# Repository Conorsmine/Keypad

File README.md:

# Keypad
Current progress on the project:

## Resources
ai03 Guide:       https://wiki.ai03.com/books/pcb-design/page/pcb-guide-part-5---creating-the-pcb  
Masterzen Guide:  https://www.masterzen.fr/2020/10/20/designing-a-keyboard-part3/

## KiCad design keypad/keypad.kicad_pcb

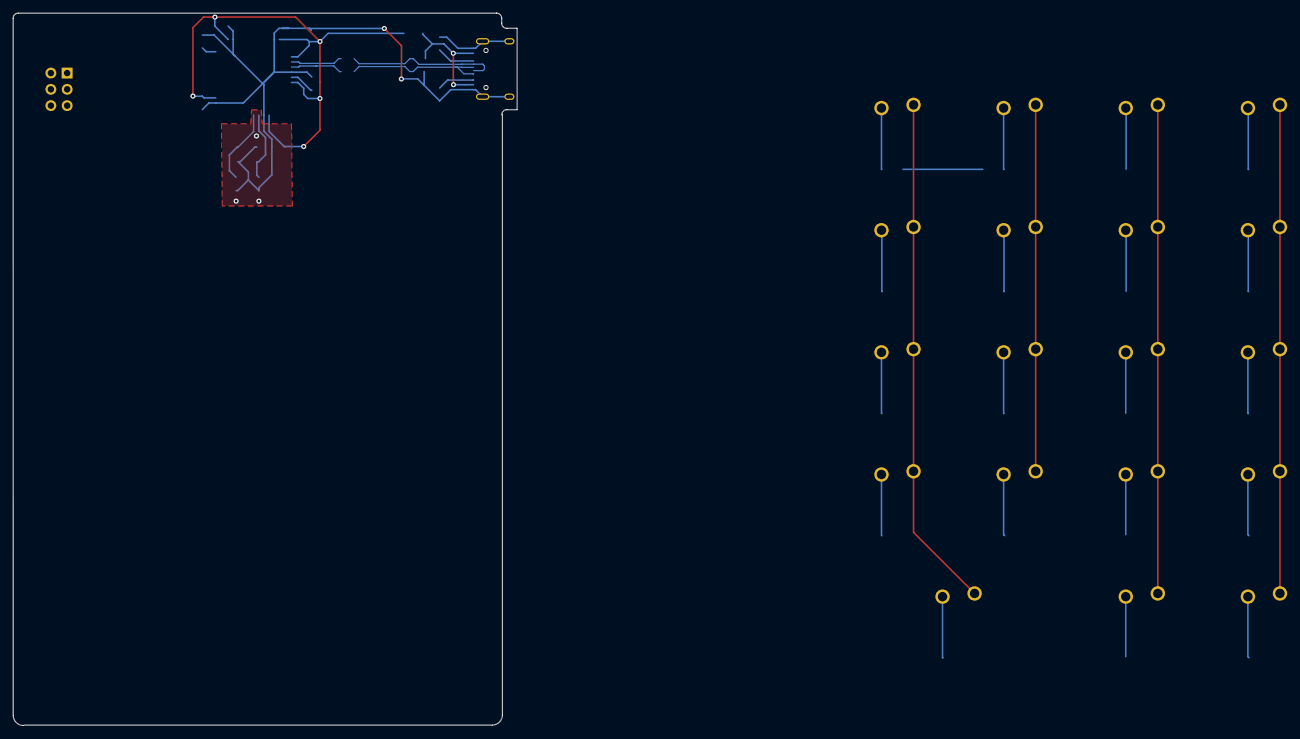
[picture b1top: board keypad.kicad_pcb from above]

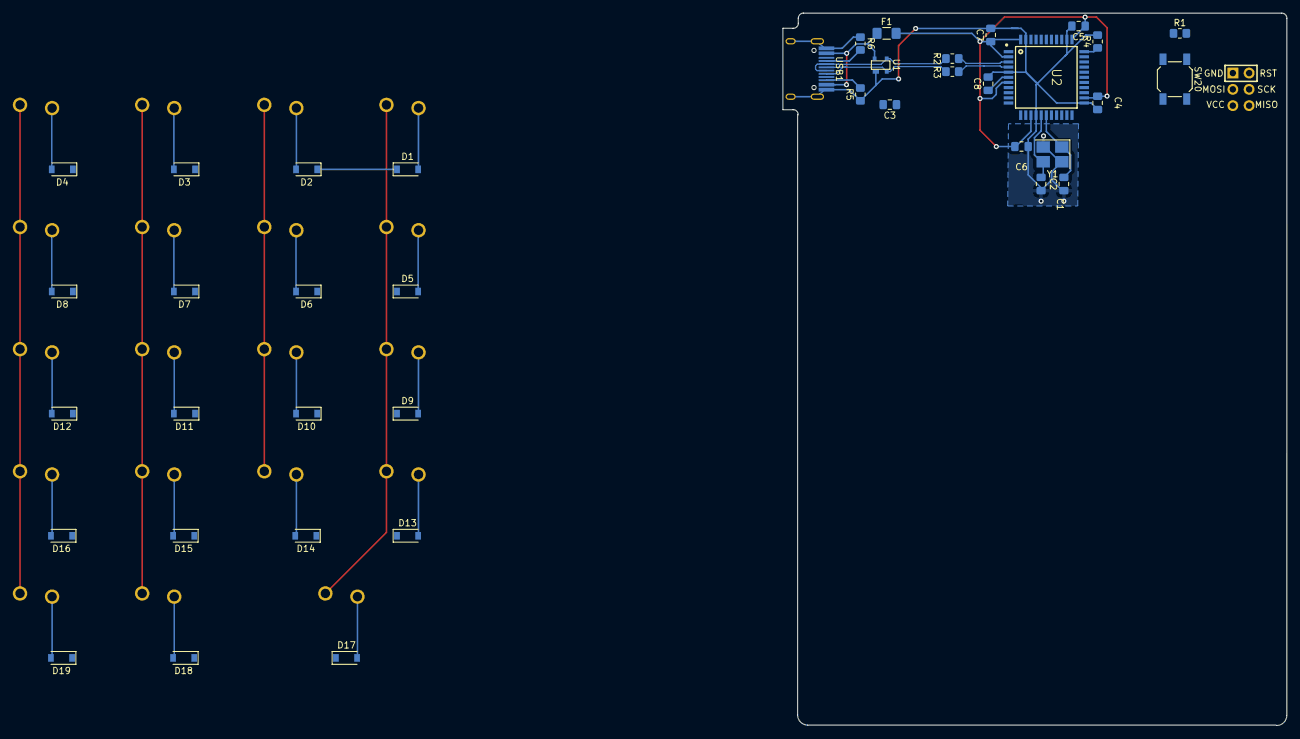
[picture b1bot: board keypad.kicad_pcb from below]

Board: 2 copper layers, 78.6 x 111.1 mm, 59 parts (40 on the bottom side), 45 nets.

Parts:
C1, C2: 22p; C_0805_2012Metric_Pad1.18x1.45mm_HandSolder
C3, C4, C5, C6: 0.1u; C_0805_2012Metric_Pad1.18x1.45mm_HandSolder
C7: 10u; C_0805_2012Metric_Pad1.18x1.45mm_HandSolder
C8: 1u; C_0805_2012Metric_Pad1.18x1.45mm_HandSolder
D1, D2, D3, D4, D5, D6, D7, D8, D9, D10, D11, D12, D13, D14, D15, D16, D17, D18, D19: D; D_SOD-123
F1: 500mA; Fuse_1206_3216Metric_Pad1.42x1.75mm_HandSolder
J1: AVR-ISP-6; Reset_Pretty-Mask
R1, R4: 10k; R_0805_2012Metric_Pad1.20x1.40mm_HandSolder
R2, R3: 22; R_0805_2012Metric_Pad1.20x1.40mm_HandSolder
R5, R6: 5.1k; R_0805_2012Metric_Pad1.20x1.40mm_HandSolder
SW1: num; ALPS-1U
SW2: div; ALPS-1U
SW3: mult; ALPS-1U
SW4: min; ALPS-1U
SW5: #7; ALPS-1U
SW6: #8; ALPS-1U
SW7: #9; ALPS-1U
SW8: plu0; ALPS-1U
SW9: #4; ALPS-1U
SW10: #5; ALPS-1U
SW11: #6; ALPS-1U
SW12: plu1; ALPS-1U
SW13: #1; ALPS-1U
SW14: #2; ALPS-1U
SW15: #3; ALPS-1U
SW16: ent0; ALPS-1U
SW17: #0; ALPS-2U
SW18: kom; ALPS-1U
SW19: ent1; ALPS-1U
SW20: SW_Push_Reset; SW_SPST_SKQG_WithStem
U1: PRTR5V0U2X; SOT143B
U2: ATMEGA32U4-AU; QFP80P1200X1200X120-44N
USB1: HRO-TYPE-C-31-M-12; HRO-TYPE-C-31-M-12-HandSoldering
Y1: XTAL; Crystal_SMD_3225-4Pin_3.2x2.5mm_HandSoldering

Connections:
+5V: C3.1, C4.1, C5.1, C6.1, C7.1, F1.2, J1.2 (VCC), R1.1, U2.2 (UVCC), U2.7 (VBUS), U2.14 (VCC), U2.24 (AVCC), U2.34 (VCC), U2.44 (AVCC)
/D+: R3.2, U2.4 (D+)
/D-: R2.2, U2.3 (D-)
/MISO: J1.1 (MISO), U2.11 (PB3)
/MOSI: J1.4 (MOSI), U2.10 (PB2)
/Reset: J1.5 (~RST), R1.2, SW20.1 (Pass), U2.13 (~RESET)
/SCK: J1.3 (SCK), U2.9 (PB1)
/XTAL1: C1.1, U2.17 (XTAL1), Y1.1
/XTAL2: C2.1, U2.16 (XTAL2), Y1.3
DN: R2.1, U1.3 (IO2), USB1.5 (DN2), USB1.7 (DN1)
DP: R3.1, U1.2 (IO1), USB1.6 (DP1), USB1.8 (DP2)
GND: C1.2, C2.2, C3.2, C4.2, C5.2, C6.2, C7.2, C8.2, J1.6 (GND), R4.2, R5.1, R6.1, SW20.2 (ve), U1.1 (GND), U2.5 (UGND), U2.15 (GND), U2.23 (GND), U2.35 (GND), U2.43 (GND), USB1.1 (GND), USB1.12 (GND), USB1.13 (SHIELD), Y1.2, Y1.4
unnamed: C8.1, U2.6 (UCAP)
unnamed: D1.2 (A), SW1.1
unnamed: D2.2 (A), SW2.1
unnamed: D3.2 (A), SW3.1
unnamed: D4.2 (A), SW4.1
unnamed: D5.2 (A), SW5.1
unnamed: D6.2 (A), SW6.1
unnamed: D7.2 (A), SW7.1
unnamed: D8.2 (A), SW8.1
unnamed: D9.2 (A), SW9.1
unnamed: D10.2 (A), SW10.1
unnamed: D11.2 (A), SW11.1
unnamed: D12.2 (A), SW12.1
unnamed: D13.2 (A), SW13.1
unnamed: D14.2 (A), SW14.1
unnamed: D15.2 (A), SW15.1
unnamed: D16.2 (A), SW16.1
unnamed: D17.2 (A), SW17.1
unnamed: D18.2 (A), SW18.1
unnamed: D19.2 (A), SW19.1
unnamed: R4.1, U2.33 (PE2)
unnamed: R5.2, USB1.10 (CC2)
unnamed: R6.2, USB1.4 (CC1)
VCC: F1.1, U1.4 (VCC), USB1.2 (VBUS), USB1.11 (VBUS)
col0: SW1.2, SW5.2, SW9.2, SW13.2, SW17.2, U2.32 (PC7)
col1: SW2.2, SW6.2, SW10.2, SW14.2, U2.31 (PC6)
col2: SW3.2, SW7.2, SW11.2, SW15.2, SW18.2, U2.29 (PB5)
col3: SW4.2, SW8.2, SW12.2, SW16.2, SW19.2, U2.30 (PB6)
row0: D1.1 (K), D2.1 (K), D3.1 (K), D4.1 (K), U2.22 (PD5)
row1: D5.1 (K), D6.1 (K), D7.1 (K), D8.1 (K), U2.21 (PD3)
row2: D9.1 (K), D10.1 (K), D11.1 (K), D12.1 (K), U2.20 (PD2)
row3: D13.1 (K), D14.1 (K), D15.1 (K), D16.1 (K), U2.19 (PD1)
row4: D17.1 (K), D18.1 (K), D19.1 (K), U2.18 (PD0)

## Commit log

2023-01-17 init
2023-01-17 Add submodules
2023-01-17 Add Footprint Libraries
2023-01-17 Add ATmega32u4
2023-01-17 Redo
2023-01-17 Add more submodules
2023-01-17 Add symbol and footprints
2023-01-17 Add ATMEGA32U4-AU librarie
2023-01-17 Scheme 1.0 complete
2023-01-17 Creat Matrix 1.0
2023-01-17 Assign Footprints
2023-01-17 PCB Layout
2023-01-17 Add Main layout
    Note that some of the layering is probably wrong. Check that again.
2023-01-18 Fixed Layering
    Also as a note, there was a rogue 1uF capacitor which I now just placed under the usb, out of the way. It may be needed later.
2023-01-18 Started Routing
2023-01-18 Removed Routing and Replaced components
2023-01-19 Routed D-Pair and Matrix
2023-01-27 Routed crystal oscillator
2023-01-27 Added ground plane
2023-01-27 Routed USB VCC
2023-01-27 Added 5V and GND routes to MCU
2023-01-27 Connected 5V/GND to USB
